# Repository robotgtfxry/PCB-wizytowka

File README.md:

# PCB wizytówka — CH32V003 + 128 × LED 0603 (rev 4.1)

Wizytówka w formacie karty ISO (**85.6 × 54 mm**, FR4 **0.8 mm**, czarna matowa maska, ENIG):

* **front:** ekran **16 × 8 = 128 diod LED 0603**, każda obrócona o **45°**, raster 2.54 mm
  (ekran ok. **40 × 20 mm**), oraz **2 super płaskie przyciski** (A/B, 3.7 × 3.7 × **0.35 mm**),
* **tył:** **CH32V003F4P6**, 3 drabinki rezystorowe 4×33 Ω, kondensatory, P-MOSFET
  zabezpieczający przed odwrotną baterią, pady pogo SWIO,
* **CR2032 bez żadnego koszyka** — trzyma ją **widelec z jednym językiem wycięty w samej karcie**,
* **tekstura z miedzi:** wylewki GND na obu stronach mają wzór **Seigaiha** (japońskie łuski fal:
  nakładające się wachlarze koncentrycznych półokręgów, łuska o promieniu 2.54 mm = raster diod),
  widoczny pod czarną matową maską; wzór ma 0.35 mm odstępu od każdej innej sieci,
* **obrys jak w układach w.cz.:** odkryty pierścień miedzi (ENIG, 0.6 mm, 0.45 mm od krawędzi)
  na obu stronach, z płotem przelotek co 2 mm, prowadzony też wokół szczelin i języka.
  **Celowo nie jest podłączony do niczego** (nie ma sieci) — to ozdoba,
* **język pod napięciem:** przód języka to siatka Seigaiha z pełnym obrzeżem w sieci **+BATT**
  (zamiast jednej prostej ścieżki), połączona z paskiem (+) i trzema przelotkami za korzeniem,
* **okno ekranu:** pod matrycą (z obu stron) jest gładkie okno bez wzoru, obwiedzione cienką
  linią masy wtopioną we wzór; dookoła wzór dochodzi do samych ścieżek (kawałki odcięte przez
  okablowanie matrycy zostają jako pływająca miedź, zamiast zostawiać poszarpane dziury),
* **tył:** ramka z narożników nad trasowaniem matrycy, taka sama jak na froncie.

| Front (izometria) | Tył (izometria) |
|---|---|
|  |  |

| Front | Tył |
|---|---|
|  |  |

> Rendery używają prostych modeli 3D z `hardware/lib/3d` (pudełka/walce generowane przez
> `gen/models3d.py`), bo w systemie nie ma pakietu `kicad-packages3d`. Język jest na renderze
> płaski — w rzeczywistości jest odgięty za baterię.

## Uchwyt baterii: widelec z jednym językiem

```
 widok z frontu                                            widok z boku
 ┌──────────────────────────────────────────┐
 │  ramię widelca (karta)            [−pad] │             karta   ══════[−]══════
 │ ═══════════ język ═══════════[ + ]═══════  ← koniec     bateria       [██████████]
 │  ramię widelca (karta)            [−pad] │   języka    język   ═══\____[+]_______
 └──────────────────────────────────────────┘
```

* Dwie szczeliny biegną od prawej krawędzi karty w lewo. Pasek między nimi to **język**: wolny
  przy krawędzi, przyczepiony ok. 43 mm dalej (32 mm od środka ogniwa). Karta po obu stronach
  szczelin to **ramiona widelca**.
* Język jest **zwężany**: 5.6 mm pod baterią (mieści się między padami (−)), poszerza się do
  10 mm przy korzeniu. Moment gnący rośnie w stronę korzenia, a razem z nim szerokość, więc
  odkształcenie rozkłada się na całą długość i język może być krótszy. Szczeliny kończą się
  okrągłymi odciążeniami Ø1.6 mm.
* Bateria leży **płasko na tyle karty**, biegunem **(−) do karty**. Ramiona mają 2 pady (−)
  blisko środka ogniwa (r < 7 mm), czyli na denku. Brzeg tej strony ogniwa (+) leży tylko na masce.
* Język jest odgięty za baterię i odsłoniętym paskiem (+) od frontu dociska biegun (+).
  Kontakt (+) może być w dowolnym miejscu tej strony, więc nie ma tu ryzyka zwarcia — cała miedź
  na przodzie języka to i tak +BATT.
* Odkryty obrys nie biegnie tam, gdzie mógłby dotknąć ogniwa naraz po stronie (−) i (+):
  na przodzie języka i na ramionach pod ogniwem (B.Cu).
* Szacunek (`python gen/fork.py`, FR4 E ≈ 20 GPa): ugięcie języka ok. 4.3 mm, długość do
  baterii ok. 22.5 mm, odkształcenie laminatu ok. **0.91%**, docisk ok. 8.7 N.
  Płytka ma 0.8 mm właśnie po to: przy 1.6 mm tak krótki język pękałby (≈ 1.8%).

**Wkładanie:** złap koniec języka przy krawędzi karty i odegnij go do tyłu (ok. 4.5 mm),
wsuń CR2032 od prawej krawędzi między kartę a język, **(−) do karty**, i puść.

Grubość: ok. 4.0 mm na baterii, ok. 4.8 mm w miejscu języka.

## Elektronika

**Charlieplexing, 12 linii (L0…L11), 128 diod, bez pustych pól:**

* wiersze ekranu = szyny L0…L7 (F.Cu); lewy-górny pad każdej diody leży na szynie swojego wiersza,
* kolumna 0: 8 diod między liniami Q (L8…L11),
* kolumny 1–8: kolumny Q (L8…L11, każda dwa razy, w obu kierunkach),
* kolumny 9–15: klasyczne kolumny „dzielone” (pary L↔L); szyna kolumny zmienia linię na
  przekątnej i łączy się z odpowiednią szyną wiersza.

Mapa diod (ref, kolumna, wiersz, linia/pin anody i katody): `fab/card/led-map.csv`.

| Linia | L0 | L1 | L2 | L3 | L4 | L5 | L6 | L7 | L8 | L9 | L10 | L11 |
|---|---|---|---|---|---|---|---|---|---|---|---|---|
| Pin MCU | PD6 | PD5 | PD4 | PD3 | PD2 | PC7 | PC6 | PC5 | PC4 | PC3 | PC2 | PC1 |

| Funkcja | Pin |
|---|---|
| Przycisk A / B | PA1 / PA2 (do GND, włącz wewnętrzny pull-up) |
| SWIO | PD1 (pad pogo na tyle) |
| wolne | PC0, PD0, PD7/NRST |

* Każda linia ma szeregowo 33 Ω (prąd LED płynie przez dwa rezystory).
* Pobór w uśpieniu (standby + budzenie EXTI z przycisku) to ok. 10 µA, więc wyłącznik nie jest potrzebny.
* **Programowanie:** WCH-LinkE → pady pogo 3V3 / SWIO / GND (raster 2.54 mm).
  ⚠ Gdy bateria jest włożona, **nie podłączaj 3V3** — tylko SWIO + GND.

## BOM (`fab/card/card-bom.csv`)

| Ilość | Ref | Część | Strona |
|---|---|---|---|
| 128 | D1–D128 | LED 0603 **żółto-zielona 565–575 nm** (AlGaInP, Vf ≈ 2.0 V) | front |
| 2 | SW1, SW2 | tact switch **3.7 × 3.7 × 0.35 mm** z kopułką: E-Switch TL3312NF160Q / C&K PTS540 / Shou Han TS3735PA | front |
| 1 | U1 | CH32V003F4P6 (TSSOP-20) | tył |
| 3 | RN1–RN3 | drabinka 4 × 33 Ω, 4×0402 convex (YC164 / CAY16) | tył |
| 1 | C1 | 100 nF 0402 | tył |
| 1 | C2 | 22 µF 0805 6.3 V | tył |
| 1 | Q1 | AO3401A (SOT-23) | tył |
| 1 | BT1 | CR2032 (sam ogniwo, bez koszyka) | tył |

Czysta zieleń (InGaN, Vf ≈ 2.8–3.1 V) z CR2032 będzie ledwo świecić. Żółto-zielona też
wygląda na zieloną.

## Montaż (dwie strony)

1. **Front na hotplate:** pasta przez stencil (`F.Paste`), 128 diod + 2 przyciski, reflow.
   Orientacja diod: `fab/card/card-assembly-top.pdf` (Fab pokazuje katodę). Połowa diod ma
   obrót 135°, połowa −45° — to celowe, wszystkie leżą na tej samej przekątnej.
2. **Tył ręcznie / hot air** (front jest już polutowany, więc hotplate odpada): U1, RN1–RN3,
   C1, C2, Q1 — `fab/card/card-assembly-bottom.pdf`.
3. Włożenie baterii (patrz wyżej).

Pozycje i obroty obu stron: `fab/card/card-cpl.csv`.

## Zamówienie (np. JLCPCB)

`fab/card/card-gerbers.zip` — 2 warstwy, **0.8 mm**, czarna matowa maska, biały sitodruk, ENIG.
Via 0.3/0.5 mm, ścieżki ≥ 0.15 mm, prześwit 0.15 mm, szczeliny języka 1.0 mm (zwykłe frezowanie).
Wylewki mają wzór Seigaiha (linie miedzi 0.3 mm) — to celowa tekstura, nie błąd. Odkryty
obrys z przelotkami przy krawędzi jest niepodłączony (bez sieci), a kawałki wzoru odcięte przez
ścieżki matrycy też są pływające — dlatego reguła DRC „isolated copper” jest w projekcie wyłączona.
Pod przyciskami (2.3 × 3.6 mm między padami) nie ma miedzi — wymóg producenta.
Stencil tylko na front.

## Pliki i generowanie

| Ścieżka | Co to jest |
|---|---|
| `hardware/card/` | projekt KiCad 10 (`card.kicad_pro/.kicad_sch/.kicad_pcb`) |
| `hardware/lib/` | footprinty projektu (LED 0603 bez sitodruku, kontakty widelca CR2032) + modele 3D |
| `fab/card/` | Gerbery, BOM, CPL, PDF-y montażowe, schemat PDF, mapa LED |
| `gen/` | skrypty generujące wszystko powyżej |

Skrypty uruchamia się Pythonem z KiCada (moduł `pcbnew`); ścieżki do bibliotek i `kicad-cli`
szuka `gen/paths.py` (Linux, macOS, Windows):

```sh
python3 gen/card.py        # PCB (matryca, widelec z językiem, routing, wzór Seigaiha, netlista)
python3 gen/schematic.py   # schemat z netlisty PCB
python3 gen/fab.py         # Gerbery, BOM, CPL, PDF-y, rendery
```

Na Windows: `& "C:\Program Files\KiCad.0in\python.exe" gen/card.py` itd.

Weryfikacja (KiCad 10.0.7): DRC **0 / 0 niepołączonych**, ERC **0**, parity schemat ↔ PCB **0**.

Tekst na froncie zmienia się w `gen/card.py` (sekcja *silkscreen*) albo ręcznie w KiCadzie.
Po ręcznej edycji nie uruchamiaj ponownie `gen/card.py`, bo nadpisze plik.

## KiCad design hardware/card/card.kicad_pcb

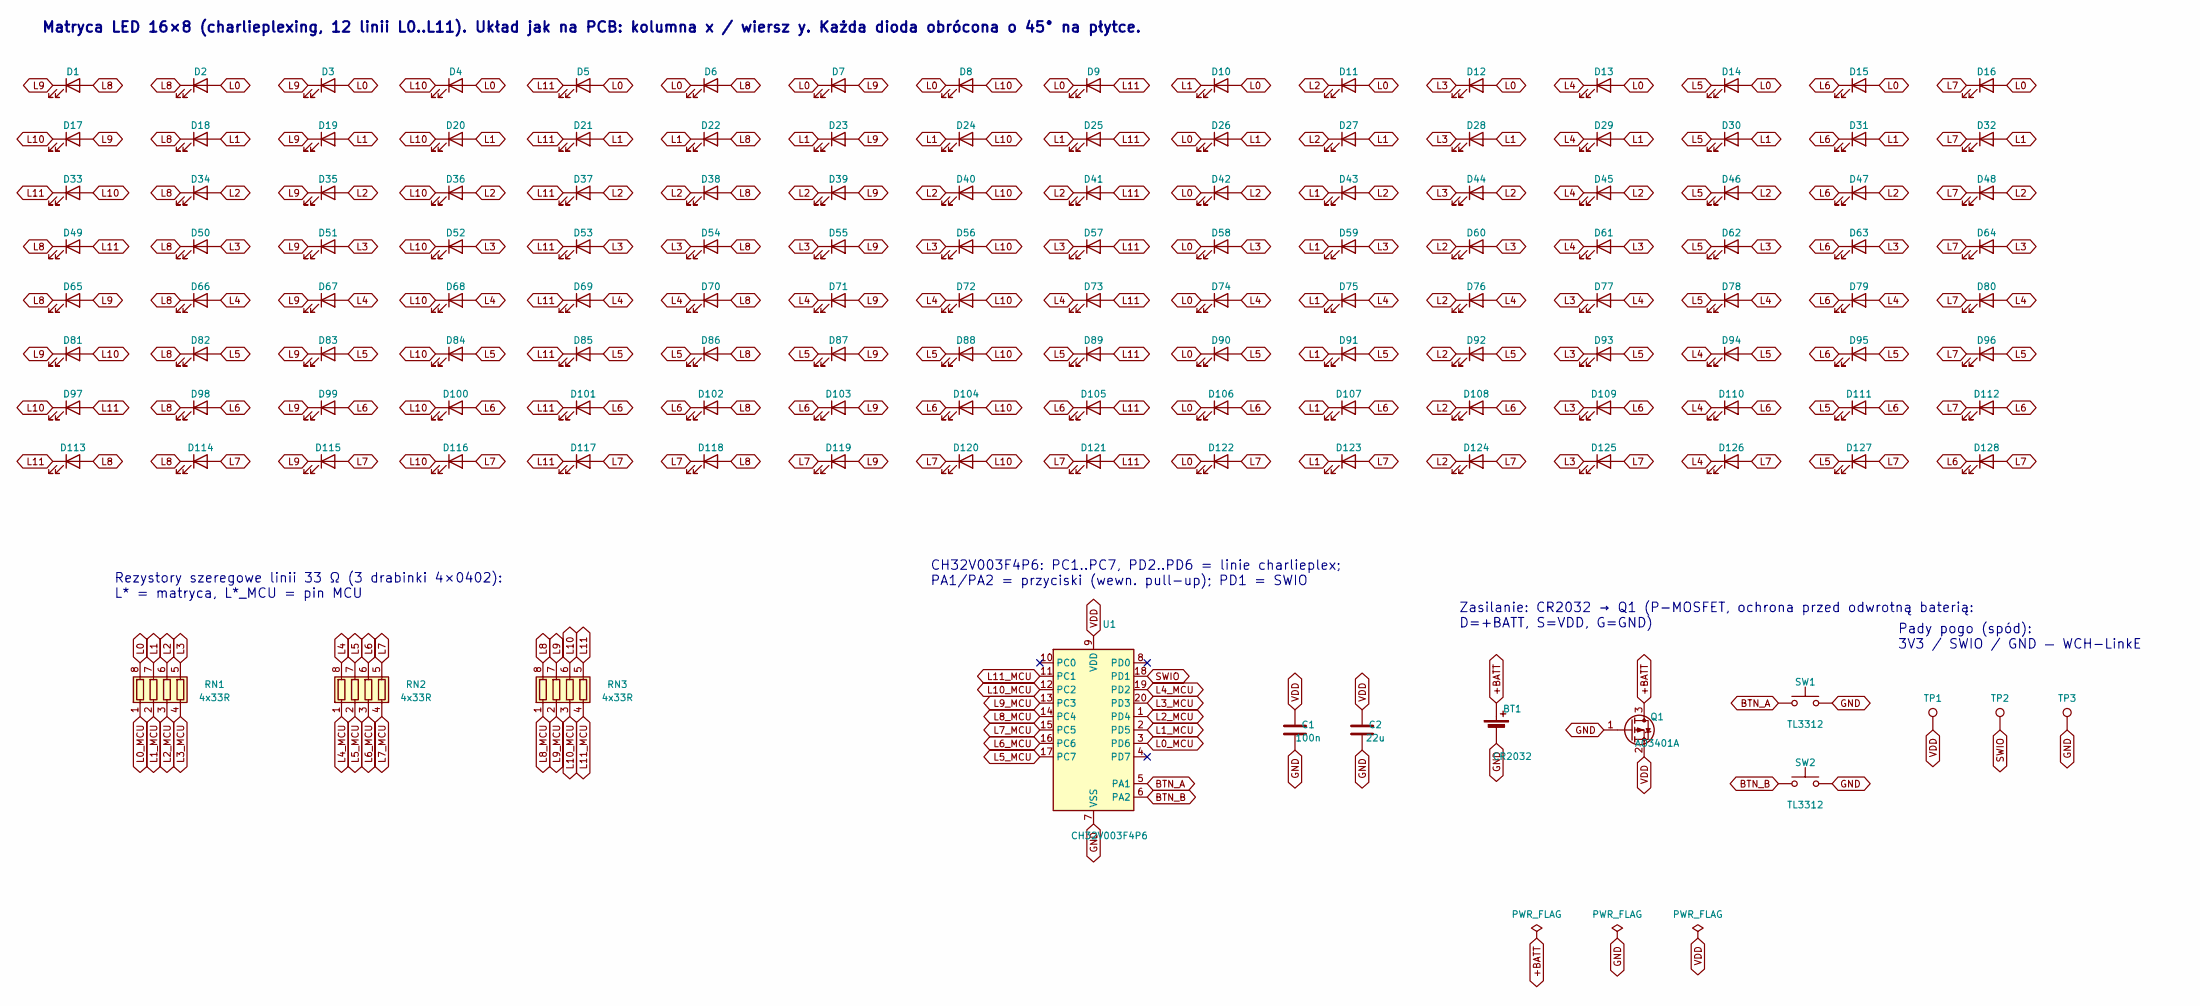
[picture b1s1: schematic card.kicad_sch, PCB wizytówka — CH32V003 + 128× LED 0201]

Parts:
BT1: CR2032; CR2032_PCB_FORK
C1: 100n; C_0402_1005Metric
C2: 22u; C_0805_2012Metric
D1, D2, D3, D4, D5, D6, D7, D8, D9, D10, D11, D12, D13, D14, D15, D16, D17, D18, D19, D20, D21, D22, D23, D24, D25, D26, D27, D28, D29, D30, D31, D32, D33, D34, D35, D36, D37, D38, D39, D40, D41, D42, D43, D44, D45, D46, D47, D48, D49, D50, D51, D52, D53, D54, D55, D56, D57, D58, D59, D60, D61, D62, D63, D64, D65, D66, D67, D68, D69, D70, D71, D72, D73, D74, D75, D76, D77, D78, D79, D80, D81, D82, D83, D84, D85, D86, D87, D88, D89, D90, D91, D92, D93, D94, D95, D96, D97, D98, D99, D100, D101, D102, D103, D104, D105, D106, D107, D108, D109, D110, D111, D112, D113, D114, D115, D116, D117, D118, D119, D120, D121, D122, D123, D124, D125, D126, D127, D128: LED_0603_YG; LED_0603_1608Metric_NoSilk
Q1: AO3401A; SOT-23
RN1, RN2, RN3: 4x33R; R_Array_Convex_4x0402
SW1, SW2: TL3312; SW_TL3312_3.7x3.7mm_H0.35mm
TP1: 3V3; TestPoint_Pad_D1.5mm
TP2: SWIO; TestPoint_Pad_D1.5mm
TP3: GND; TestPoint_Pad_D1.5mm
U1: CH32V003F4P6; TSSOP-20_4.4x6.5mm_P0.65mm

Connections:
+BATT: BT1.1 (+), Q1.3 (D)
BTN_A: SW1.1, U1.5 (PA1)
BTN_B: SW2.1, U1.6 (PA2)
GND: BT1.2 (-), C1.2, C2.2, Q1.1 (G), SW1.2, SW2.2, TP3.1, U1.7 (VSS)
L0: D2.2 (A), D3.2 (A), D4.2 (A), D5.2 (A), D6.1 (K), D7.1 (K), D8.1 (K), D9.1 (K), D10.2 (A), D11.2 (A), D12.2 (A), D13.2 (A), D14.2 (A), D15.2 (A), D16.2 (A), D26.1 (K), D42.1 (K), D58.1 (K), D74.1 (K), D90.1 (K), D106.1 (K), D122.1 (K), RN1.8 (R1.2)
L0_MCU: RN1.1 (R1.1), U1.3 (PD6)
L1: D10.1 (K), D18.2 (A), D19.2 (A), D20.2 (A), D21.2 (A), D22.1 (K), D23.1 (K), D24.1 (K), D25.1 (K), D26.2 (A), D27.2 (A), D28.2 (A), D29.2 (A), D30.2 (A), D31.2 (A), D32.2 (A), D43.1 (K), D59.1 (K), D75.1 (K), D91.1 (K), D107.1 (K), D123.1 (K), RN1.7 (R2.2)
L1_MCU: RN1.2 (R2.1), U1.2 (PD5)
L2: D11.1 (K), D27.1 (K), D34.2 (A), D35.2 (A), D36.2 (A), D37.2 (A), D38.1 (K), D39.1 (K), D40.1 (K), D41.1 (K), D42.2 (A), D43.2 (A), D44.2 (A), D45.2 (A), D46.2 (A), D47.2 (A), D48.2 (A), D60.1 (K), D76.1 (K), D92.1 (K), D108.1 (K), D124.1 (K), RN1.6 (R3.2)
L2_MCU: RN1.3 (R3.1), U1.1 (PD4)
L3: D12.1 (K), D28.1 (K), D44.1 (K), D50.2 (A), D51.2 (A), D52.2 (A), D53.2 (A), D54.1 (K), D55.1 (K), D56.1 (K), D57.1 (K), D58.2 (A), D59.2 (A), D60.2 (A), D61.2 (A), D62.2 (A), D63.2 (A), D64.2 (A), D77.1 (K), D93.1 (K), D109.1 (K), D125.1 (K), RN1.5 (R4.2)
L3_MCU: RN1.4 (R4.1), U1.20 (PD3)
L4: D13.1 (K), D29.1 (K), D45.1 (K), D61.1 (K), D66.2 (A), D67.2 (A), D68.2 (A), D69.2 (A), D70.1 (K), D71.1 (K), D72.1 (K), D73.1 (K), D74.2 (A), D75.2 (A), D76.2 (A), D77.2 (A), D78.2 (A), D79.2 (A), D80.2 (A), D94.1 (K), D110.1 (K), D126.1 (K), RN2.8 (R1.2)
L4_MCU: RN2.1 (R1.1), U1.19 (PD2)
L5: D14.1 (K), D30.1 (K), D46.1 (K), D62.1 (K), D78.1 (K), D82.2 (A), D83.2 (A), D84.2 (A), D85.2 (A), D86.1 (K), D87.1 (K), D88.1 (K), D89.1 (K), D90.2 (A), D91.2 (A), D92.2 (A), D93.2 (A), D94.2 (A), D95.2 (A), D96.2 (A), D111.1 (K), D127.1 (K), RN2.7 (R2.2)
L5_MCU: RN2.2 (R2.1), U1.17 (PC7)
L6: D15.1 (K), D31.1 (K), D47.1 (K), D63.1 (K), D79.1 (K), D95.1 (K), D98.2 (A), D99.2 (A), D100.2 (A), D101.2 (A), D102.1 (K), D103.1 (K), D104.1 (K), D105.1 (K), D106.2 (A), D107.2 (A), D108.2 (A), D109.2 (A), D110.2 (A), D111.2 (A), D112.2 (A), D128.1 (K), RN2.6 (R3.2)
L6_MCU: RN2.3 (R3.1), U1.16 (PC6)
L7: D16.1 (K), D32.1 (K), D48.1 (K), D64.1 (K), D80.1 (K), D96.1 (K), D112.1 (K), D114.2 (A), D115.2 (A), D116.2 (A), D117.2 (A), D118.1 (K), D119.1 (K), D120.1 (K), D121.1 (K), D122.2 (A), D123.2 (A), D124.2 (A), D125.2 (A), D126.2 (A), D127.2 (A), D128.2 (A), RN2.5 (R4.2)
L7_MCU: RN2.4 (R4.1), U1.15 (PC5)
L8: D1.2 (A), D2.1 (K), D6.2 (A), D18.1 (K), D22.2 (A), D34.1 (K), D38.2 (A), D49.1 (K), D50.1 (K), D54.2 (A), D65.1 (K), D66.1 (K), D70.2 (A), D82.1 (K), D86.2 (A), D98.1 (K), D102.2 (A), D113.2 (A), D114.1 (K), D118.2 (A), RN3.8 (R1.2)
L8_MCU: RN3.1 (R1.1), U1.14 (PC4)
L9: D1.1 (K), D3.1 (K), D7.2 (A), D17.2 (A), D19.1 (K), D23.2 (A), D35.1 (K), D39.2 (A), D51.1 (K), D55.2 (A), D65.2 (A), D67.1 (K), D71.2 (A), D81.1 (K), D83.1 (K), D87.2 (A), D99.1 (K), D103.2 (A), D115.1 (K), D119.2 (A), RN3.7 (R2.2)
L9_MCU: RN3.2 (R2.1), U1.13 (PC3)
L10: D4.1 (K), D8.2 (A), D17.1 (K), D20.1 (K), D24.2 (A), D33.2 (A), D36.1 (K), D40.2 (A), D52.1 (K), D56.2 (A), D68.1 (K), D72.2 (A), D81.2 (A), D84.1 (K), D88.2 (A), D97.1 (K), D100.1 (K), D104.2 (A), D116.1 (K), D120.2 (A), RN3.6 (R3.2)
L10_MCU: RN3.3 (R3.1), U1.12 (PC2)
L11: D5.1 (K), D9.2 (A), D21.1 (K), D25.2 (A), D33.1 (K), D37.1 (K), D41.2 (A), D49.2 (A), D53.1 (K), D57.2 (A), D69.1 (K), D73.2 (A), D85.1 (K), D89.2 (A), D97.2 (A), D101.1 (K), D105.2 (A), D113.1 (K), D117.1 (K), D121.2 (A), RN3.5 (R4.2)
L11_MCU: RN3.4 (R4.1), U1.11 (PC1)
SWIO: TP2.1, U1.18 (PD1)
VDD: C1.1, C2.1, Q1.2 (S), TP1.1, U1.9 (VDD)

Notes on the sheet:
Matryca LED 16×8 (charlieplexing, 12 linii L0..L11). Układ jak na PCB: kolumna x / wiersz y. Każda dioda obrócona o 45° na płytce.
Rezystory szeregowe linii 33 Ω (3 drabinki 4×0402): L* = matryca, L*_MCU = pin MCU
CH32V003F4P6: PC1..PC7, PD2..PD6 = linie charlieplex; PA1/PA2 = przyciski (wewn. pull-up); PD1 = SWIO
Zasilanie: CR2032 → Q1 (P-MOSFET, ochrona przed odwrotną baterią: D=+BATT, S=VDD, G=GND)
Pady pogo (spód): 3V3 / SWIO / GND — WCH-LinkE

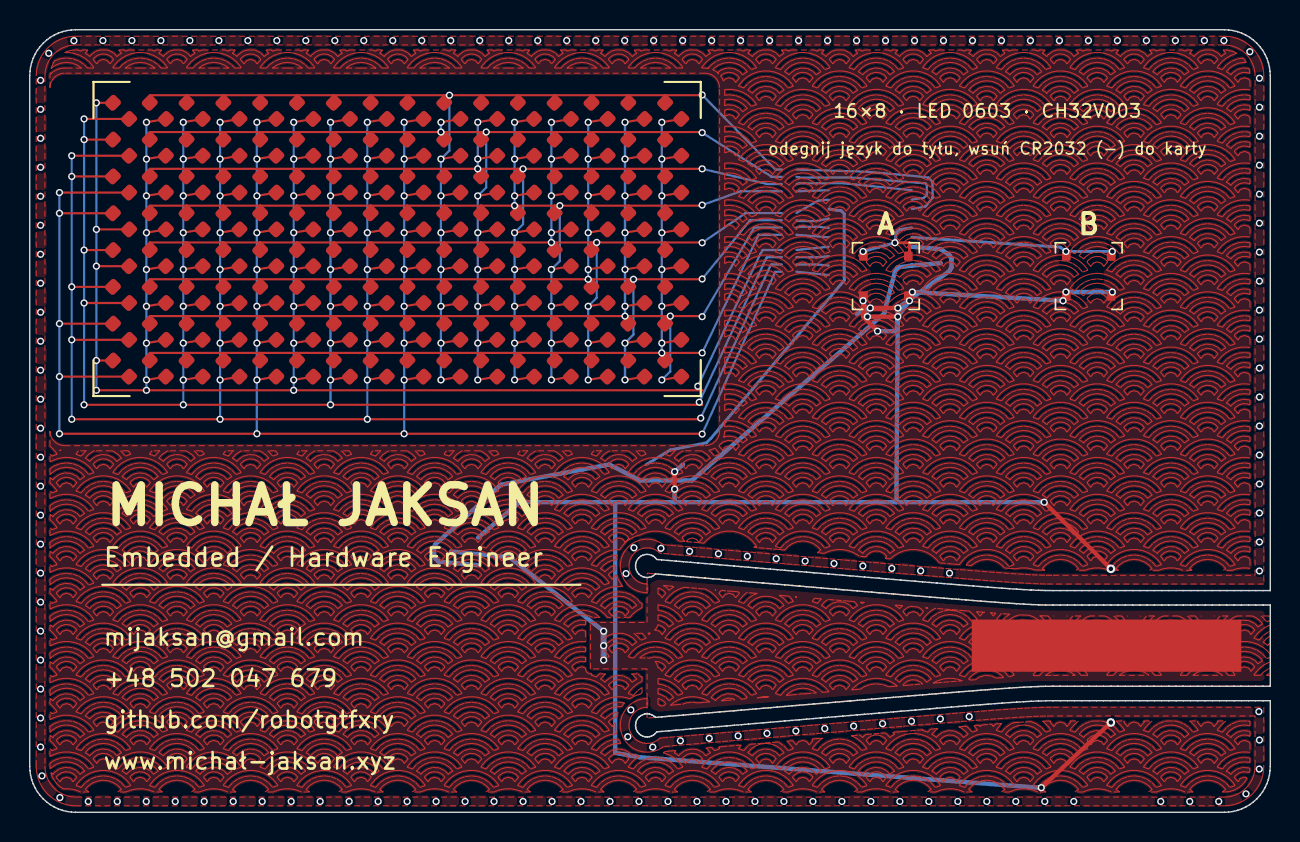
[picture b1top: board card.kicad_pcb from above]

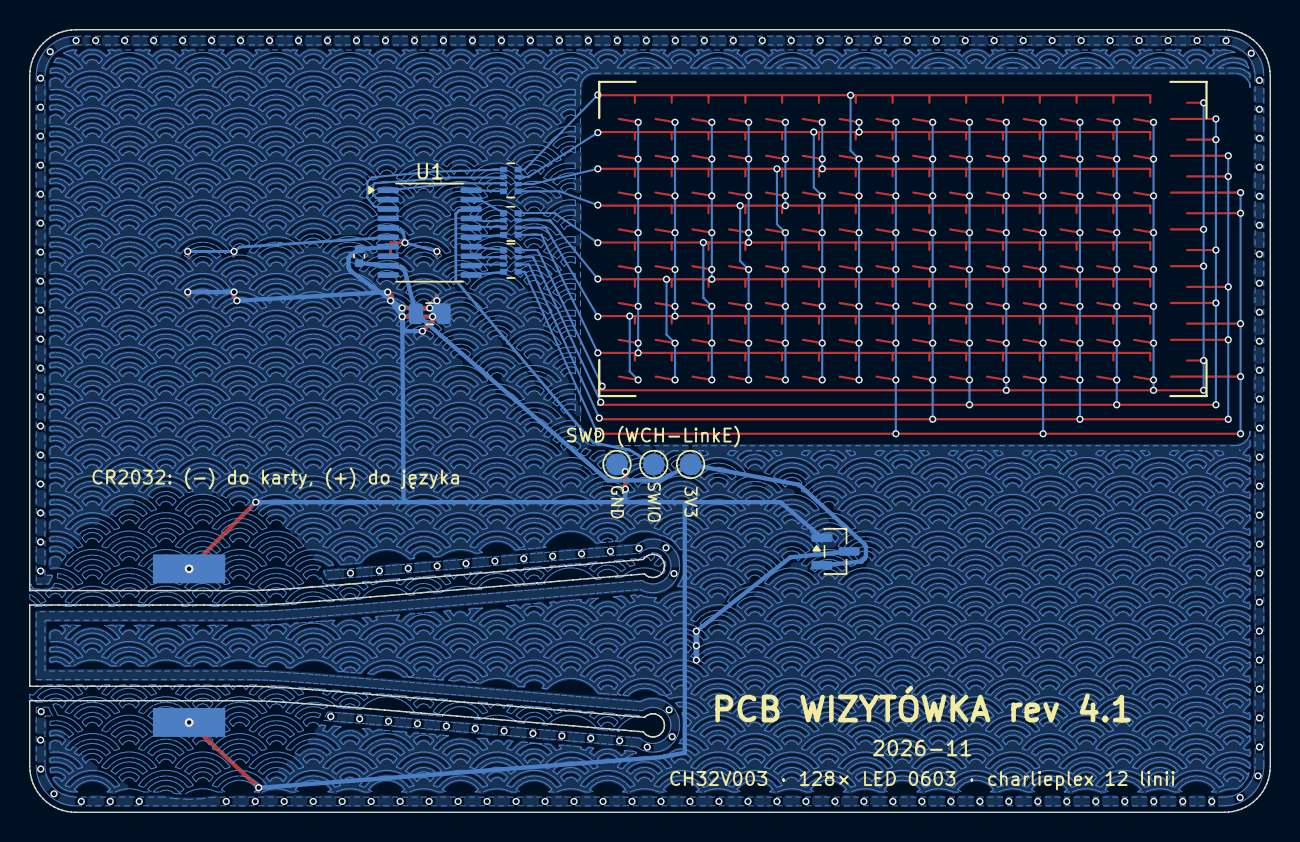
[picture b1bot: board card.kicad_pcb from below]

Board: 2 copper layers, 85.6 x 54.0 mm, 141 parts (10 on the bottom side), 30 nets.

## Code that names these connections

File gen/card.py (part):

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NL = 12
Q_COLS = [8, 9, 10, 11, 8, 9, 10, 11]          # line of Q columns x = 1..8
SPECIAL = [(8, 9), (9, 10), (10, 11), (11, 8), (9, 8), (10, 9), (11, 10), (8, 11)]  # column 0
PIN_NAME = {"1": "PD4", "2": "PD5", "3": "PD6", "4": "PD7/NRST", "5": "PA1", "6": "PA2",
            "7": "VSS", "8": "PD0", "9": "VDD", "10": "PC0", "11": "PC1", "12": "PC2",
            "13": "PC3", "14": "PC4", "15": "PC5", "16": "PC6", "17": "PC7",
            "18": "PD1/SWIO", "19": "PD2", "20": "PD3"}

BAT_C = (W - 11.0, 42.5)        # cell centre (cell lies on the back, inside the fork)

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               back=True)
    upads = {p.GetNumber(): kb.local(p.GetPosition()) for p in u1.Pads()}
    assert upads["20"][0] < UX and upads["20"][1] < upads["11"][1] and upads["1"][0] > UX
    # L0..L2 wrap over the top of the MCU onto PD6/PD5/PD4, the rest go to the left column
    line_pin = {0: "3", 1: "2", 2: "1", 3: "20", 4: "19", 5: "17", 6: "16", 7: "15",
                8: "14", 9: "13", 10: "12", 11: "11"}
    mp = {line_pin[i]: LM(i) for i in range(NL)}
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    json.dump(led_table, open(os.path.join(OUT, "led_map.json"), "w"), indent=1)
    json.dump(parts, open(os.path.join(OUT, "parts.json"), "w"), indent=1)
    pins = {L(i): PIN_NAME[line_pin[i]] for i in range(NL)}
    pins.update({"BTN_A": PIN_NAME["5"], "BTN_B": PIN_NAME["6"], "SWIO": PIN_NAME["18"]})
    json.dump(pins, open(os.path.join(OUT, "pins.json"), "w"), indent=1)
    with open(os.path.join(OUT, "fp-lib-table"), "w") as fh:
        fh.write('(fp_lib_table\n  (version 7)\n  (lib (name "wizytowka")(type "KiCad")'
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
